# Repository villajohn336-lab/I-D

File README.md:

# I-D
Digital Fabrication Final Project

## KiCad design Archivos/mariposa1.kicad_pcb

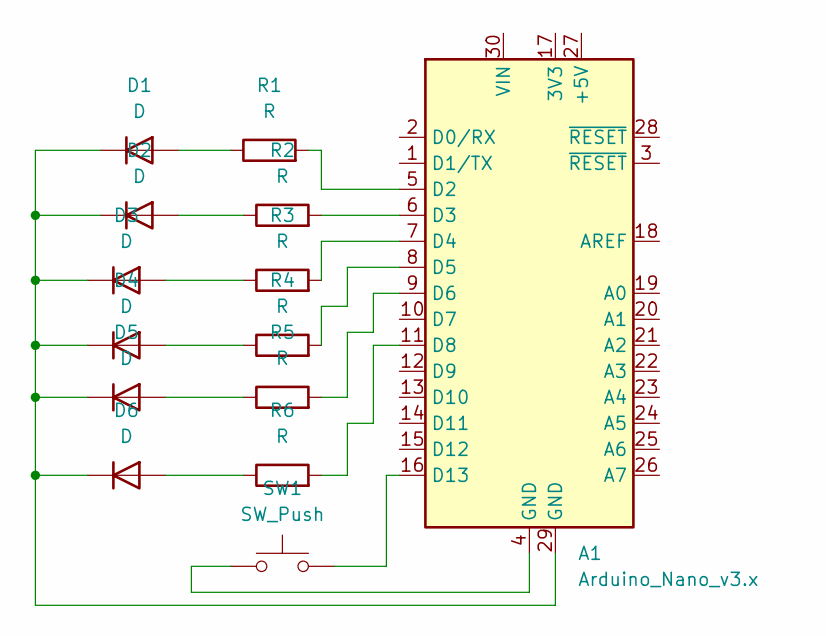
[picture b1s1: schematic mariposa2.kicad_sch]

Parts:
A1: Arduino_Nano_v3.x; Arduino_Nano
D1, D2, D3, D4, D5, D6: D; LED_D1.8mm_W3.3mm_H2.4mm_modificado
R1, R2, R3, R4, R5, R6: R; R_Axial_DIN0207_L6.3mm_D2.5mm_P7.62mm_Horizontal
SW1: SW_Push; SW_Push_1TS009xxxx-xxxx-xxxx_6x6x5mm

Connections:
unnamed: A1.5 (D2), R1.2
unnamed: A1.6 (D3), R2.2
unnamed: A1.7 (D4), R3.2
unnamed: A1.8 (D5), R4.2
unnamed: A1.9 (D6), R5.2
unnamed: A1.11 (D8), R6.2
unnamed: A1.16 (D13), SW1.2
unnamed: A1.4 (GND), SW1.1
unnamed: D1.2 (A), R1.1
unnamed: A1.29 (GND), D1.1 (K), D2.1 (K), D3.1 (K), D4.1 (K), D5.1 (K), D6.1 (K)
unnamed: D2.2 (A), R2.1
unnamed: D3.2 (A), R3.1
unnamed: D4.2 (A), R4.1
unnamed: D5.2 (A), R5.1
unnamed: D6.2 (A), R6.1

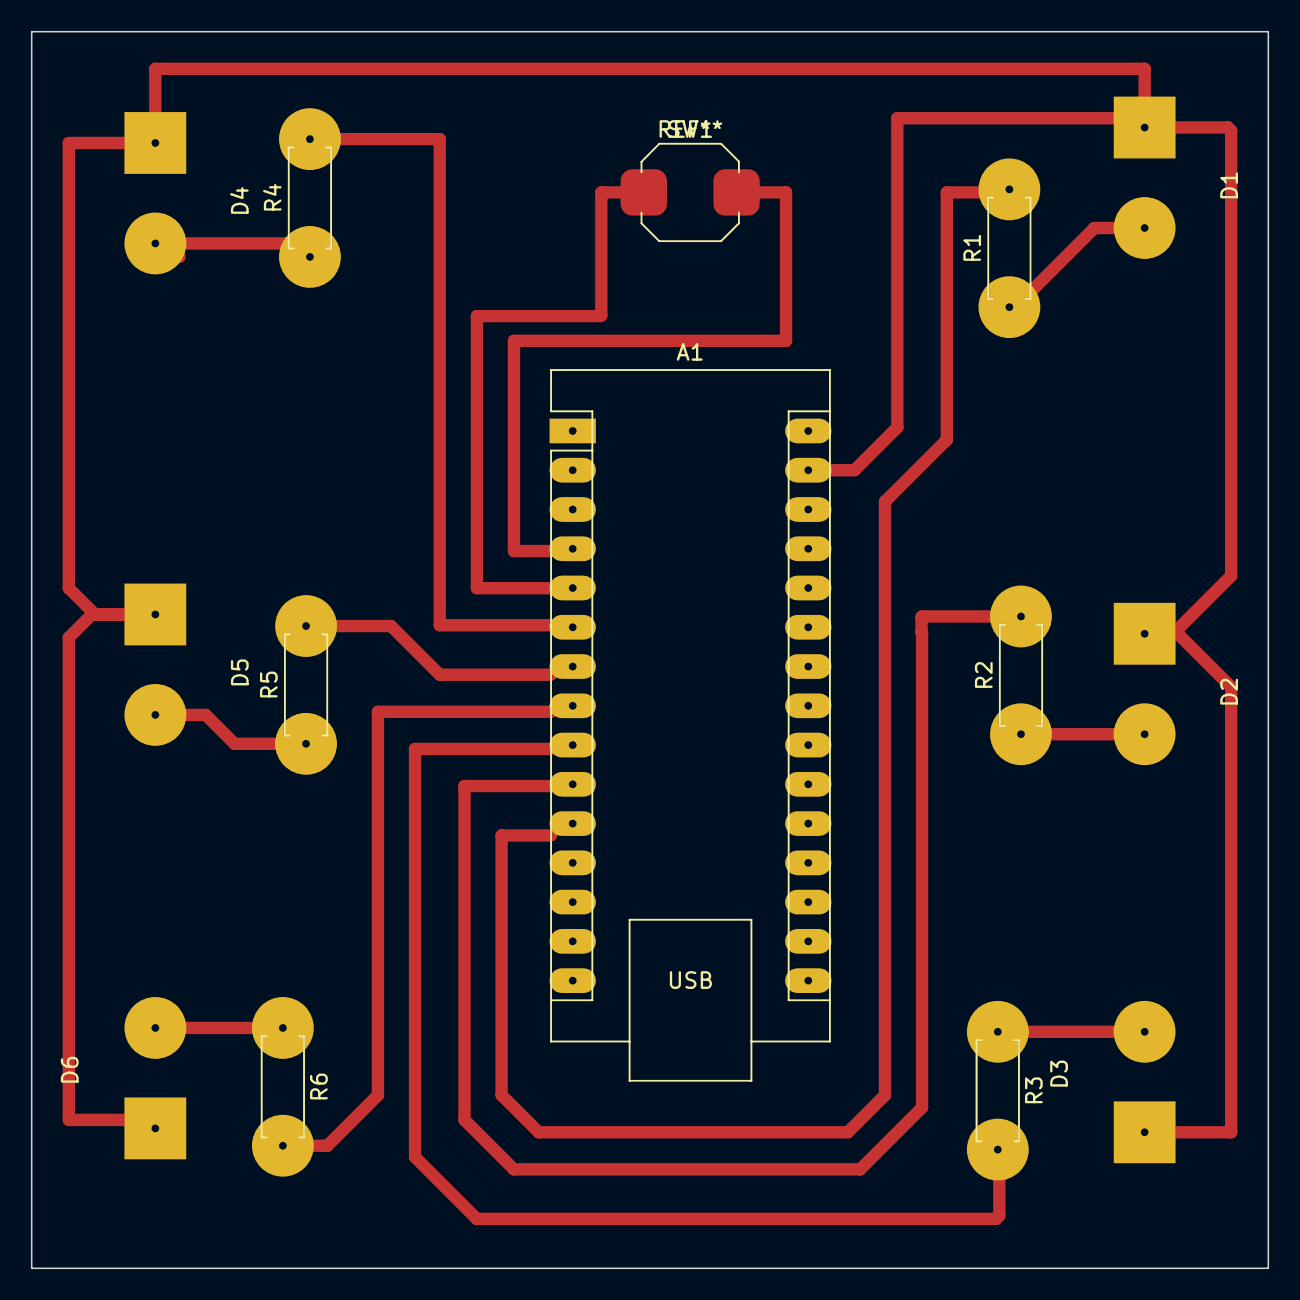
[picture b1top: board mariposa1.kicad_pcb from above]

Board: 2 copper layers, 80.0 x 80.0 mm, 14 parts (0 on the bottom side), 15 nets.
